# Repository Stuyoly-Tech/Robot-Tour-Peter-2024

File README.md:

View this project on [CADLAB.io](https://cadlab.io/project/28689). 

# Robot-Tour-Peter-2024
Petah

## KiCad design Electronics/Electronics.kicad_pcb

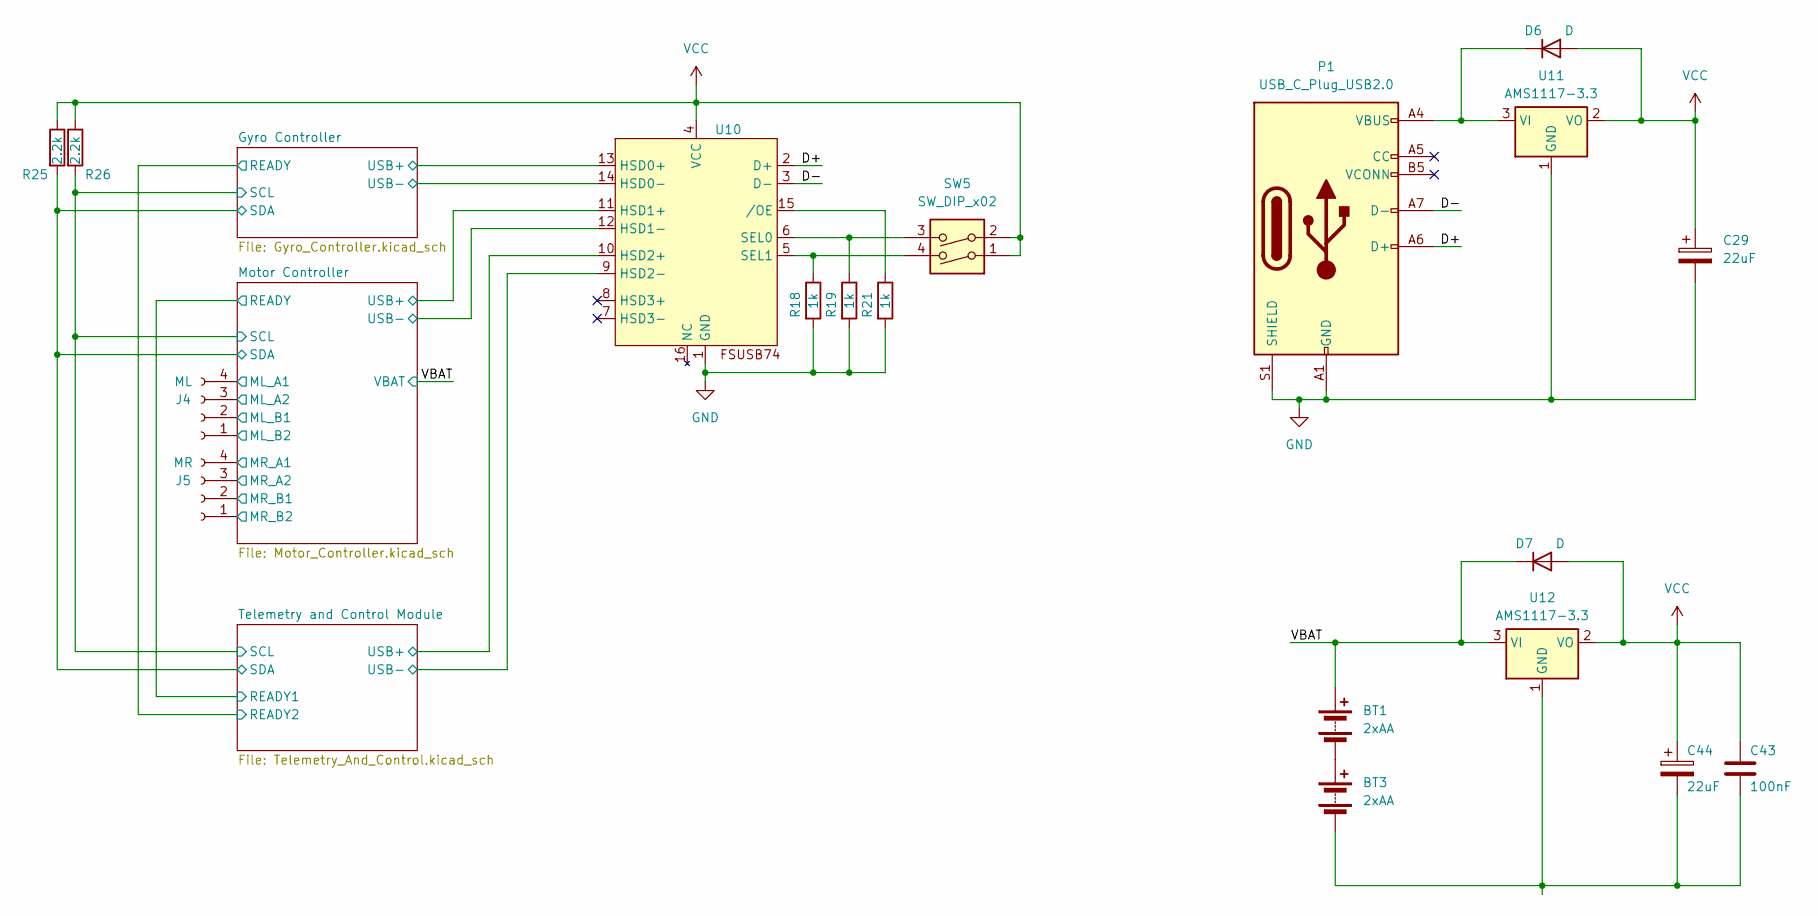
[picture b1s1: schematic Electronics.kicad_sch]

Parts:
BT1, BT3: 2xAA; BatteryHolder_Keystone_2462_2xAA
C29, C44: 22uF; CP_Elec_6.3x5.9
C43: 100nF; C_0201_0603Metric
D6, D7: D; R_0201_0603Metric
J4: ML; JST_PH_B4B-PH-K_1x04_P2.00mm_Vertical
J5: MR; JST_PH_B4B-PH-K_1x04_P2.00mm_Vertical
P1: USB_C_Plug_USB2.0; USB_C_Receptacle_Molex_105450-0101
R18, R19, R21: 1k; R_0201_0603Metric
R25, R26: 2.2k; R_0201_0603Metric
SW5: SW_DIP_x02; SW_DIP_SPSTx02_Slide_9.78x7.26mm_W8.61mm_P2.54mm
U10: QFN-16-1EP_3x3mm_P0.5mm_EP1.7x1.7mm
U11, U12: AMS1117-3.3; SOT-223-3_TabPin2

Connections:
/D+: P1.A6 (D+), U10.2 (D+)
/D-: P1.A7 (D-), U10.3 (D-)
/Gyro Controller/SCL: R26.2; also elsewhere on the board
/Gyro Controller/SDA: R25.2; also elsewhere on the board
/Gyro Controller/USB+: U10.13 (HSD0+); also elsewhere on the board
/Gyro Controller/USB-: U10.14 (HSD0-); also elsewhere on the board
/Motor Controller/ML_A1: J4.4; also elsewhere on the board
/Motor Controller/ML_A2: J4.3; also elsewhere on the board
/Motor Controller/ML_B1: J4.2; also elsewhere on the board
/Motor Controller/ML_B2: J4.1; also elsewhere on the board
/Motor Controller/MR_A1: J5.4; also elsewhere on the board
/Motor Controller/MR_A2: J5.3; also elsewhere on the board
/Motor Controller/MR_B1: J5.2; also elsewhere on the board
/Motor Controller/MR_B2: J5.1; also elsewhere on the board
/Motor Controller/USB+: U10.11 (HSD1+); also elsewhere on the board
/Motor Controller/USB-: U10.12 (HSD1-); also elsewhere on the board
/Telemetry and Control Module/USB+: U10.10 (HSD2+); also elsewhere on the board
/Telemetry and Control Module/USB-: U10.9 (HSD2-); also elsewhere on the board
/VBAT: BT1.1 (+), D7.1 (K), U12.3 (VI); also elsewhere on the board
GND: C29.2, P1.A1 (GND), P1.A12 (GND), P1.B1 (GND), P1.B12 (GND), P1.S1 (SHIELD), R18.2, R19.2, R21.2, U10.1 (GND), U11.1 (GND); also elsewhere on the board
unnamed: BT1.2 (-), BT3.1 (+)
unnamed: BT3.2 (-), C43.2, C44.2, U12.1 (GND)
unnamed: D6.1 (K), P1.A4 (VBUS), P1.A9 (VBUS), P1.B4 (VBUS), P1.B9 (VBUS), U11.3 (VI)
unnamed: R19.1, SW5.3, U10.6 (SEL0)
unnamed: R18.1, SW5.4, U10.5 (SEL1)
unnamed: R21.1, U10.15 (/OE)
VCC: C29.1, C43.1, C44.1, D6.2 (A), D7.2 (A), R25.1, R26.1, SW5.1, SW5.2, U10.4 (VCC), U11.2 (VO), U12.2 (VO); also elsewhere on the board

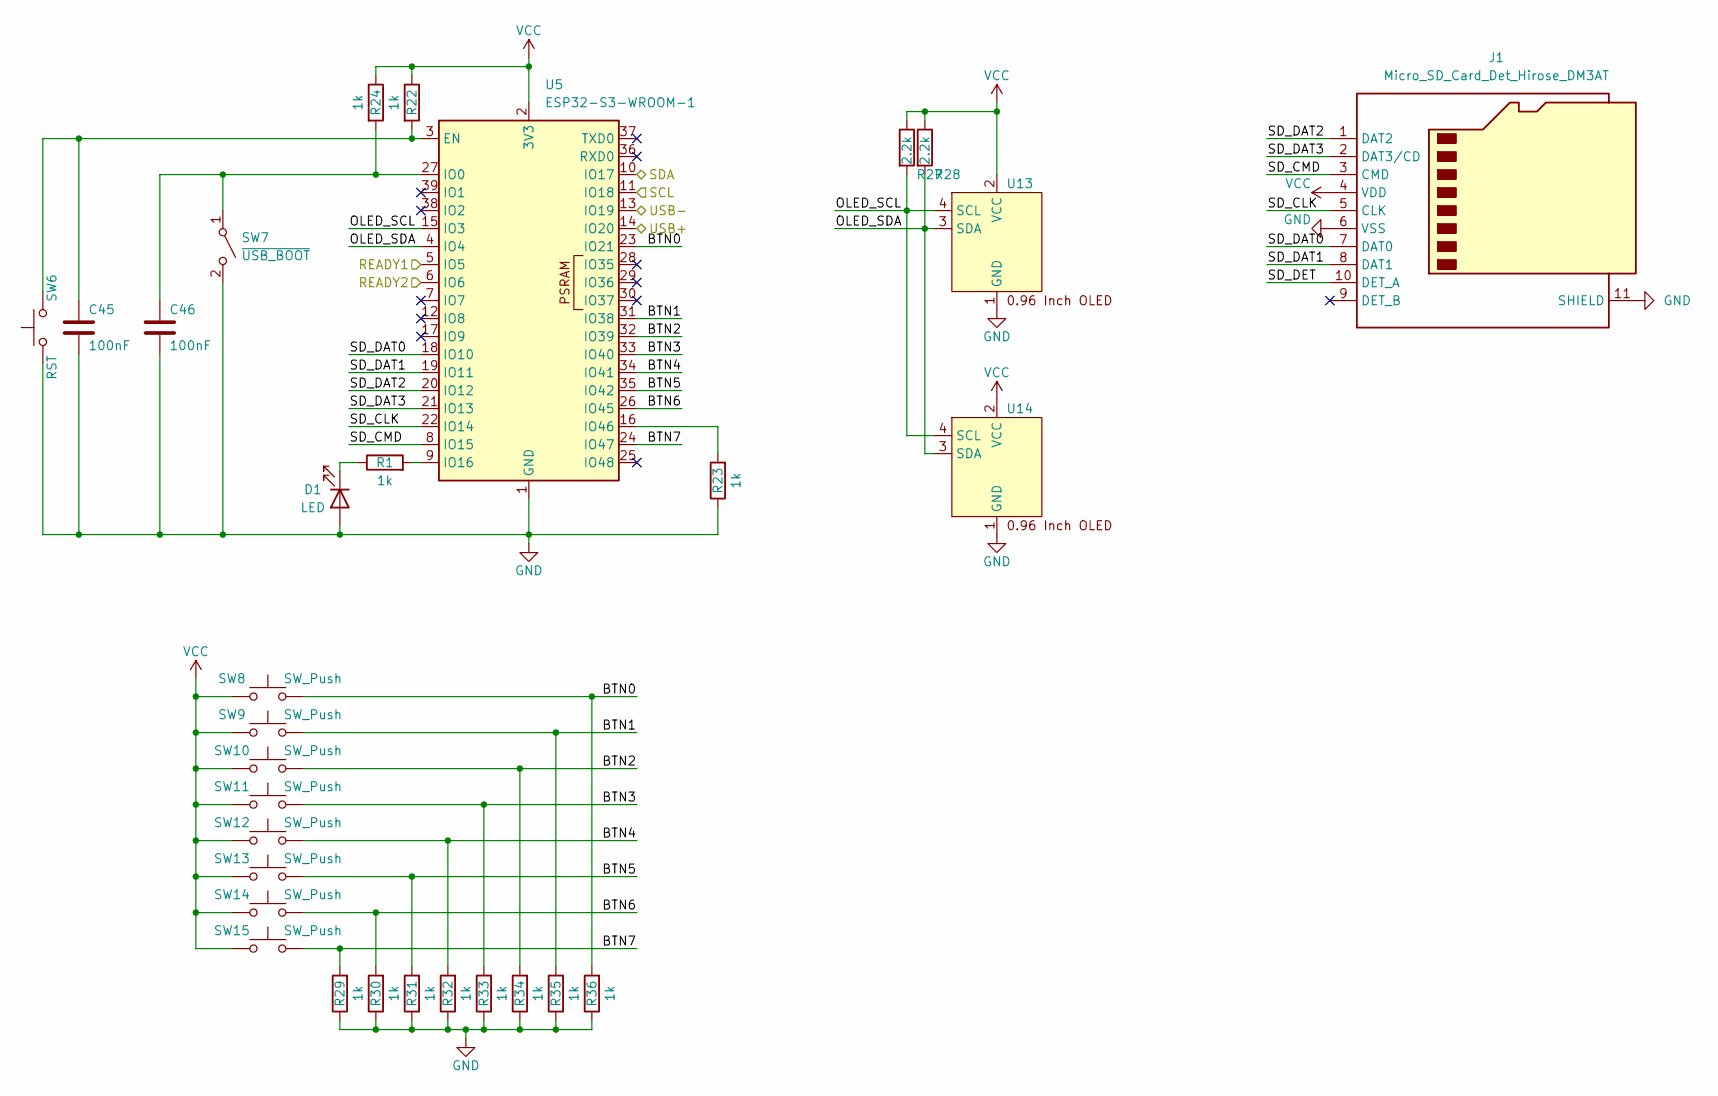
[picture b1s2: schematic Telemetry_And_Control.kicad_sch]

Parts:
C45, C46: 100nF; C_0201_0603Metric
D1: LED; LED_0603_1608Metric
J1: Micro_SD_Card_Det_Hirose_DM3AT; microSD_HC_Molex_104031-0811
R1, R22, R23, R24, R29, R30, R31, R32, R33, R34, R35, R36: 1k; R_0201_0603Metric
R27, R28: 2.2k; R_0201_0603Metric
SW6: RST; SW_SPST_TL3342
SW7: ~{USB_BOOT}; SW_DPDT_CK_JS202011JCQN
SW8, SW9, SW10, SW11, SW12, SW13, SW14, SW15: SW_Push; SW_Cherry_MX_1.00u_PCB
U5: ESP32-S3-WROOM-1
U13, U14: PinHeader_1x04_P2.54mm_Vertical

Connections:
/Gyro Controller/READY: U5.6 (IO6); also elsewhere on the board
/Gyro Controller/SCL: U5.11 (IO18); also elsewhere on the board
/Gyro Controller/SDA: U5.10 (IO17); also elsewhere on the board
/Motor Controller/READY: U5.5 (IO5); also elsewhere on the board
/Telemetry and Control Module/BTN0: R36.2, SW8.2, U5.23 (IO21)
/Telemetry and Control Module/BTN1: R35.2, SW9.2, U5.31 (IO38)
/Telemetry and Control Module/BTN2: R34.2, SW10.2, U5.32 (IO39)
/Telemetry and Control Module/BTN3: R33.2, SW11.2, U5.33 (IO40)
/Telemetry and Control Module/BTN4: R32.2, SW12.2, U5.34 (IO41)
/Telemetry and Control Module/BTN5: R31.2, SW13.2, U5.35 (IO42)
/Telemetry and Control Module/BTN6: R30.2, SW14.2, U5.26 (IO45)
/Telemetry and Control Module/BTN7: R29.2, SW15.2, U5.24 (IO47)
/Telemetry and Control Module/OLED_SCL: R27.2, U5.15 (IO3), U13.4 (SCL), U14.4 (SCL)
/Telemetry and Control Module/OLED_SDA: R28.2, U5.4 (IO4), U13.3 (SDA), U14.3 (SDA)
/Telemetry and Control Module/SD_CLK: J1.5 (CLK), U5.22 (IO14)
/Telemetry and Control Module/SD_CMD: J1.3 (CMD), U5.8 (IO15)
/Telemetry and Control Module/SD_DAT0: J1.7 (DAT0), U5.18 (IO10)
/Telemetry and Control Module/SD_DAT1: J1.8 (DAT1), U5.19 (IO11)
/Telemetry and Control Module/SD_DAT2: J1.1 (DAT2), U5.20 (IO12)
/Telemetry and Control Module/SD_DAT3: J1.2 (DAT3/CD), U5.21 (IO13)
/Telemetry and Control Module/SD_DET: J1.10 (DET_A)
/Telemetry and Control Module/USB+: U5.14 (IO20); also elsewhere on the board
/Telemetry and Control Module/USB-: U5.13 (IO19); also elsewhere on the board
GND: C45.2, C46.2, D1.2 (A), J1.6 (VSS), J1.11 (SHIELD), R23.1, R29.1, R30.1, R31.1, R32.1, R33.1, R34.1, R35.1, R36.1, SW6.1, SW7.2 (B), U5.1 (GND), U5.40 (GND), U5.41 (GND), U13.1 (GND), U14.1 (GND); also elsewhere on the board
unnamed: D1.1 (K), R1.1
unnamed: C46.1, R24.2, SW7.1 (A), U5.27 (IO0)
unnamed: C45.1, R22.2, SW6.2, U5.3 (EN)
unnamed: R1.2, U5.9 (IO16)
unnamed: R23.2, U5.16 (IO46)
VCC: J1.4 (VDD), R22.1, R24.1, R27.1, R28.1, SW8.1, SW9.1, SW10.1, SW11.1, SW12.1, SW13.1, SW14.1, SW15.1, U5.2 (3V3), U13.2 (VCC), U14.2 (VCC); also elsewhere on the board

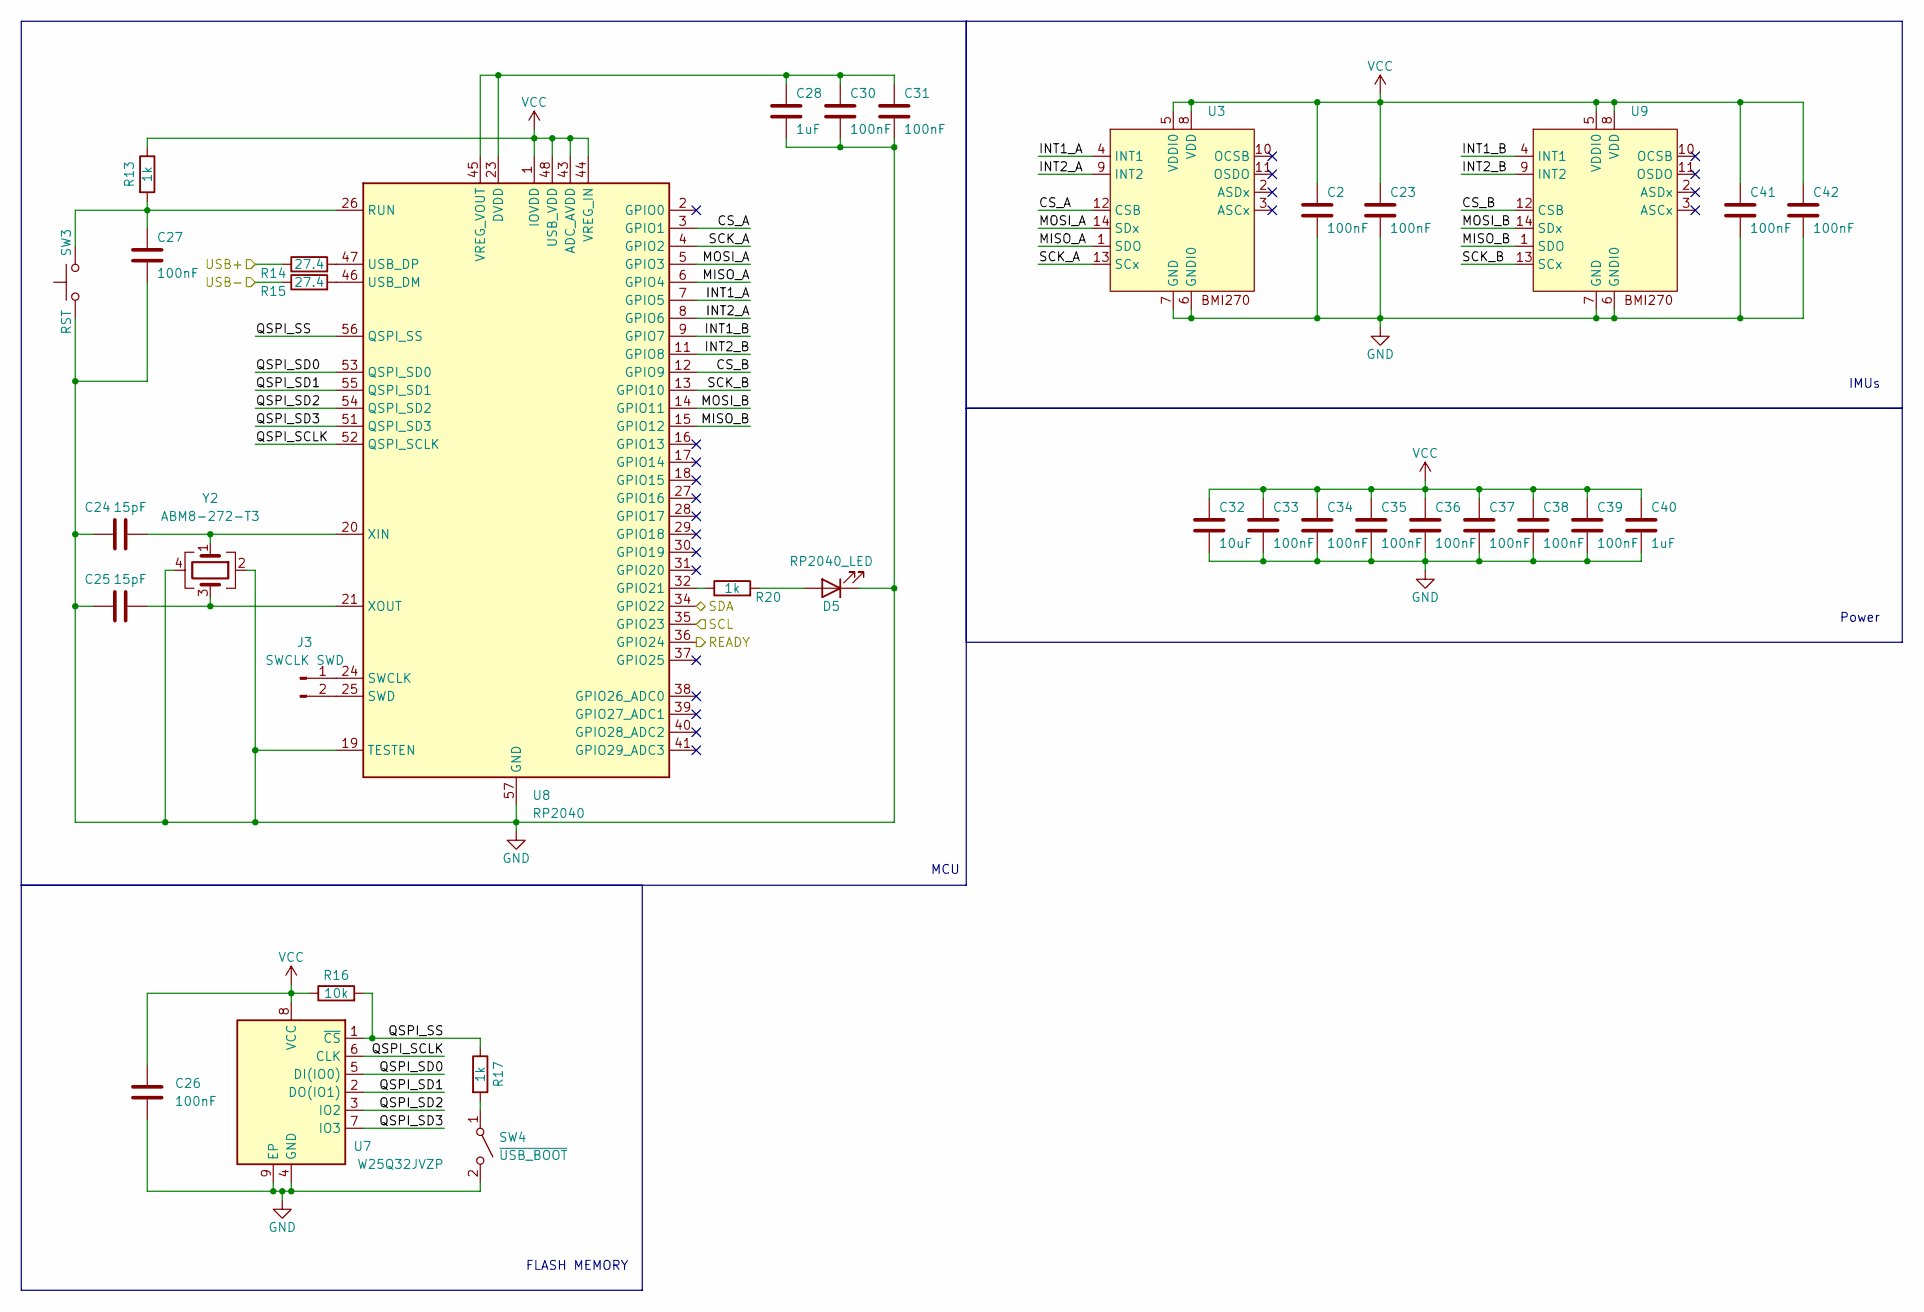
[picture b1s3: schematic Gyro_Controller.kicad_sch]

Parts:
C2, C23, C26, C27, C30, C31, C33, C34, C35, C36, C37, C38, C39, C41, C42: 100nF; C_0201_0603Metric
C24, C25: 15pF; C_0201_0603Metric
C28, C40: 1uF; C_0201_0603Metric
C32: 10uF; C_0201_0603Metric
D5: RP2040_LED; LED_0603_1608Metric
J3: SWCLK SWD; PinHeader_1x02_P2.54mm_Vertical
R13, R17, R20: 1k; R_0201_0603Metric
R14, R15: 27.4; R_0201_0603Metric
R16: 10k; R_0201_0603Metric
SW3: RST; SW_SPST_TL3342
SW4: ~{USB_BOOT}; SW_DPDT_CK_JS202011JCQN
U3, U9: Bosch_LGA-14_3x2.5mm_P0.5mm
U7: W25Q32JVZP; WSON-8-1EP_6x5mm_P1.27mm_EP3.4x4.3mm
U8: RP2040; QFN-56-1EP_7x7mm_P0.4mm_EP3.2x3.2mm
Y2: ABM8-272-T3; Crystal_SMD_Abracon_ABM8G-4Pin_3.2x2.5mm

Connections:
/Gyro Controller/CS_A: U3.12 (CSB), U8.3 (GPIO1)
/Gyro Controller/CS_B: U8.12 (GPIO9), U9.12 (CSB)
/Gyro Controller/INT1_A: U3.4 (INT1), U8.7 (GPIO5)
/Gyro Controller/INT1_B: U8.9 (GPIO7), U9.4 (INT1)
/Gyro Controller/INT2_A: U3.9 (INT2), U8.8 (GPIO6)
/Gyro Controller/INT2_B: U8.11 (GPIO8), U9.9 (INT2)
/Gyro Controller/MISO_A: U3.1 (SDO), U8.6 (GPIO4)
/Gyro Controller/MISO_B: U8.15 (GPIO12), U9.1 (SDO)
/Gyro Controller/MOSI_A: U3.14 (SDx), U8.5 (GPIO3)
/Gyro Controller/MOSI_B: U8.14 (GPIO11), U9.14 (SDx)
/Gyro Controller/QSPI_SCLK: U7.6 (CLK), U8.52 (QSPI_SCLK)
/Gyro Controller/QSPI_SD0: U7.5 (DI(IO0)), U8.53 (QSPI_SD0)
/Gyro Controller/QSPI_SD1: U7.2 (DO(IO1)), U8.55 (QSPI_SD1)
/Gyro Controller/QSPI_SD2: U7.3 (IO2), U8.54 (QSPI_SD2)
/Gyro Controller/QSPI_SD3: U7.7 (IO3), U8.51 (QSPI_SD3)
/Gyro Controller/QSPI_SS: R16.2, R17.1, U7.1 (~CS), U8.56 (QSPI_SS)
/Gyro Controller/READY: U8.36 (GPIO24); also elsewhere on the board
/Gyro Controller/SCK_A: U3.13 (SCx), U8.4 (GPIO2)
/Gyro Controller/SCK_B: U8.13 (GPIO10), U9.13 (SCx)
/Gyro Controller/SCL: U8.35 (GPIO23); also elsewhere on the board
/Gyro Controller/SDA: U8.34 (GPIO22); also elsewhere on the board
/Gyro Controller/USB+: R14.1; also elsewhere on the board
/Gyro Controller/USB-: R15.1; also elsewhere on the board
GND: C2.2, C23.2, C24.1, C25.1, C26.2, C27.2, C28.2, C30.2, C31.2, C32.2, C33.2, C34.2, C35.2, C36.2, C37.2, C38.2, C39.2, C40.2, C41.2, C42.2, D5.1 (K), SW3.1, SW4.2 (B), U3.6 (GNDI0), U3.7 (GND), U7.4 (GND), U7.9 (EP), U8.19 (TESTEN), U8.57 (GND), U9.6 (GNDI0), U9.7 (GND), Y2.2, Y2.4; also elsewhere on the board
unnamed: D5.2 (A), R20.2
unnamed: J3.1, U8.24 (SWCLK)
unnamed: J3.2, U8.25 (SWD)
unnamed: R17.2, SW4.1 (A)
unnamed: R20.1, U8.32 (GPIO21)
unnamed: C27.1, R13.2, SW3.2, U8.26 (RUN)
unnamed: R15.2, U8.46 (USB_DM)
unnamed: R14.2, U8.47 (USB_DP)
unnamed: C28.1, C30.1, C31.1, U8.23 (DVDD), U8.45 (VREG_VOUT), U8.50 (DVDD)
unnamed: C24.2, U8.20 (XIN), Y2.1
unnamed: C25.2, U8.21 (XOUT), Y2.3
VCC: C2.1, C23.1, C26.1, C32.1, C33.1, C34.1, C35.1, C36.1, C37.1, C38.1, C39.1, C40.1, C41.1, C42.1, R13.1, R16.1, U3.5 (VDDI0), U3.8 (VDD), U7.8 (VCC), U8.1 (IOVDD), U8.10 (IOVDD), U8.22 (IOVDD), U8.33 (IOVDD), U8.42 (IOVDD), U8.43 (ADC_AVDD), U8.44 (VREG_IN), U8.48 (USB_VDD), U8.49 (IOVDD), U9.5 (VDDI0), U9.8 (VDD); also elsewhere on the board

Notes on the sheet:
Power
IMUs
MCU
FLASH MEMORY

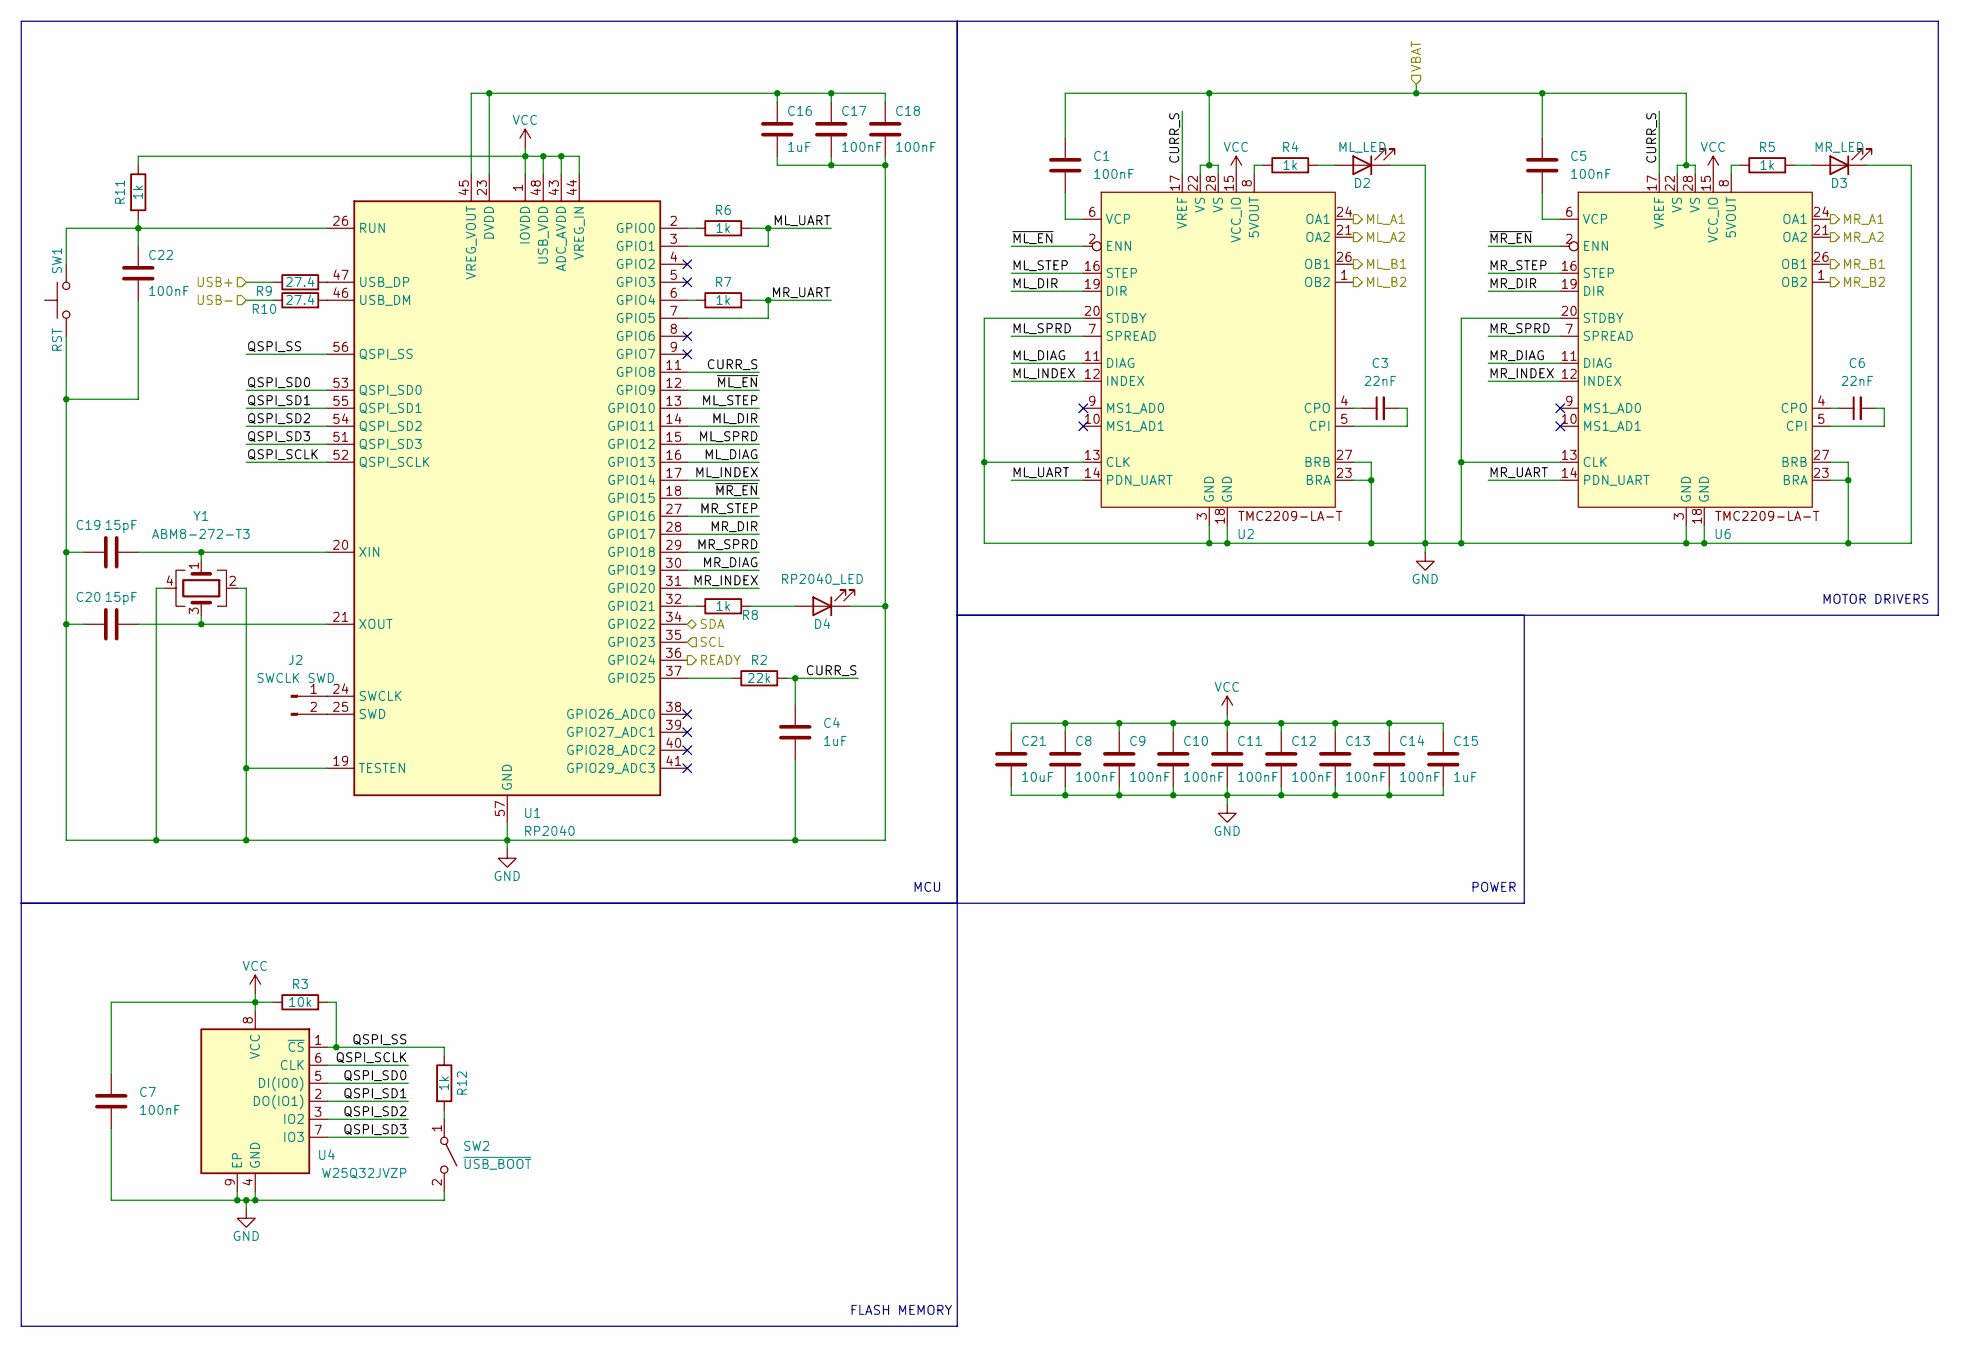
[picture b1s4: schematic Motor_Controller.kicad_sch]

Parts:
C1, C5, C7, C8, C9, C10, C11, C12, C13, C14, C17, C18, C22: 100nF; C_0201_0603Metric
C3, C6: 22nF; C_0201_0603Metric
C4, C15, C16: 1uF; C_0201_0603Metric
C19, C20: 15pF; C_0201_0603Metric
C21: 10uF; C_0201_0603Metric
D2: ML_LED; LED_0603_1608Metric
D3: MR_LED; LED_0603_1608Metric
D4: RP2040_LED; LED_0603_1608Metric
J2: SWCLK SWD; PinHeader_1x02_P2.54mm_Vertical
R2: 22k; R_0201_0603Metric
R3: 10k; R_0201_0603Metric
R4, R5, R6, R7, R8, R11, R12: 1k; R_0201_0603Metric
R9, R10: 27.4; R_0201_0603Metric
SW1: RST; SW_SPST_TL3342
SW2: ~{USB_BOOT}; SW_DPDT_CK_JS202011JCQN
U1: RP2040; QFN-56-1EP_7x7mm_P0.4mm_EP3.2x3.2mm
U2, U6: QFN-28-1EP_5x5mm_P0.5mm_EP3.75x3.75mm
U4: W25Q32JVZP; WSON-8-1EP_6x5mm_P1.27mm_EP3.4x4.3mm
Y1: ABM8-272-T3; Crystal_SMD_Abracon_ABM8G-4Pin_3.2x2.5mm

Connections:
/Gyro Controller/SCL: U1.35 (GPIO23); also elsewhere on the board
/Gyro Controller/SDA: U1.34 (GPIO22); also elsewhere on the board
/Motor Controller/CURR_S: C4.1, R2.2, U1.11 (GPIO8), U2.17 (VREF), U6.17 (VREF)
/Motor Controller/ML_A1: U2.24 (OA1); also elsewhere on the board
/Motor Controller/ML_A2: U2.21 (OA2); also elsewhere on the board
/Motor Controller/ML_B1: U2.26 (OB1); also elsewhere on the board
/Motor Controller/ML_B2: U2.1 (OB2); also elsewhere on the board
/Motor Controller/ML_DIAG: U1.16 (GPIO13), U2.11 (DIAG)
/Motor Controller/ML_DIR: U1.14 (GPIO11), U2.19 (DIR)
/Motor Controller/ML_INDEX: U1.17 (GPIO14), U2.12 (INDEX)
/Motor Controller/ML_SPRD: U1.15 (GPIO12), U2.7 (SPREAD)
/Motor Controller/ML_STEP: U1.13 (GPIO10), U2.16 (STEP)
/Motor Controller/ML_UART: R6.2, U1.3 (GPIO1), U2.14 (PDN_UART)
/Motor Controller/MR_A1: U6.24 (OA1); also elsewhere on the board
/Motor Controller/MR_A2: U6.21 (OA2); also elsewhere on the board
/Motor Controller/MR_B1: U6.26 (OB1); also elsewhere on the board
/Motor Controller/MR_B2: U6.1 (OB2); also elsewhere on the board
/Motor Controller/MR_DIAG: U1.30 (GPIO19), U6.11 (DIAG)
/Motor Controller/MR_DIR: U1.28 (GPIO17), U6.19 (DIR)
/Motor Controller/MR_INDEX: U1.31 (GPIO20), U6.12 (INDEX)
/Motor Controller/MR_SPRD: U1.29 (GPIO18), U6.7 (SPREAD)
/Motor Controller/MR_STEP: U1.27 (GPIO16), U6.16 (STEP)
/Motor Controller/MR_UART: R7.2, U1.7 (GPIO5), U6.14 (PDN_UART)
/Motor Controller/QSPI_SCLK: U1.52 (QSPI_SCLK), U4.6 (CLK)
/Motor Controller/QSPI_SD0: U1.53 (QSPI_SD0), U4.5 (DI(IO0))
/Motor Controller/QSPI_SD1: U1.55 (QSPI_SD1), U4.2 (DO(IO1))
/Motor Controller/QSPI_SD2: U1.54 (QSPI_SD2), U4.3 (IO2)
/Motor Controller/QSPI_SD3: U1.51 (QSPI_SD3), U4.7 (IO3)
/Motor Controller/QSPI_SS: R3.2, R12.1, U1.56 (QSPI_SS), U4.1 (~CS)
/Motor Controller/READY: U1.36 (GPIO24); also elsewhere on the board
/Motor Controller/USB+: R9.1; also elsewhere on the board
/Motor Controller/USB-: R10.1; also elsewhere on the board
/Motor Controller/~ML_EN: U1.12 (GPIO9), U2.2 (ENN)
/Motor Controller/~MR_EN: U1.18 (GPIO15), U6.2 (ENN)
/VBAT: C1.1, C5.1, U2.22 (VS), U2.28 (VS), U6.22 (VS), U6.28 (VS); also elsewhere on the board
GND: C4.2, C7.2, C8.2, C9.2, C10.2, C11.2, C12.2, C13.2, C14.2, C15.2, C16.2, C17.2, C18.2, C19.1, C20.1, C21.2, C22.2, D2.1 (K), D3.1 (K), D4.1 (K), SW1.1, SW2.2 (B), U1.19 (TESTEN), U1.57 (GND), U2.3 (GND), U2.13 (CLK), U2.18 (GND), U2.20 (STDBY), U2.23 (BRA), U2.27 (BRB), U4.4 (GND), U4.9 (EP), U6.3 (GND), U6.13 (CLK), U6.18 (GND), U6.20 (STDBY), U6.23 (BRA), U6.27 (BRB), Y1.2, Y1.4; also elsewhere on the board
unnamed: D2.2 (A), R4.2
unnamed: D3.2 (A), R5.2
unnamed: D4.2 (A), R8.2
unnamed: J2.1, U1.24 (SWCLK)
unnamed: J2.2, U1.25 (SWD)
unnamed: R12.2, SW2.1 (A)
unnamed: R6.1, U1.2 (GPIO0)
unnamed: R7.1, U1.6 (GPIO4)
unnamed: R8.1, U1.32 (GPIO21)
unnamed: R2.1, U1.37 (GPIO25)
unnamed: C22.1, R11.2, SW1.2, U1.26 (RUN)
unnamed: R10.2, U1.46 (USB_DM)
unnamed: R9.2, U1.47 (USB_DP)
unnamed: C16.1, C17.1, C18.1, U1.23 (DVDD), U1.45 (VREG_VOUT), U1.50 (DVDD)
unnamed: C19.2, U1.20 (XIN), Y1.1
unnamed: C20.2, U1.21 (XOUT), Y1.3
unnamed: R4.1, U2.8 (5VOUT)
unnamed: C3.2, U2.5 (CPI)
unnamed: C3.1, U2.4 (CPO)
unnamed: C1.2, U2.6 (VCP)
unnamed: R5.1, U6.8 (5VOUT)
unnamed: C6.2, U6.5 (CPI)
unnamed: C6.1, U6.4 (CPO)
unnamed: C5.2, U6.6 (VCP)
VCC: C7.1, C8.1, C9.1, C10.1, C11.1, C12.1, C13.1, C14.1, C15.1, C21.1, R3.1, R11.1, U1.1 (IOVDD), U1.10 (IOVDD), U1.22 (IOVDD), U1.33 (IOVDD), U1.42 (IOVDD), U1.43 (ADC_AVDD), U1.44 (VREG_IN), U1.48 (USB_VDD), U1.49 (IOVDD), U2.15 (VCC_IO), U4.8 (VCC), U6.15 (VCC_IO); also elsewhere on the board

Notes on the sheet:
MCU
FLASH MEMORY
POWER
MOTOR DRIVERS

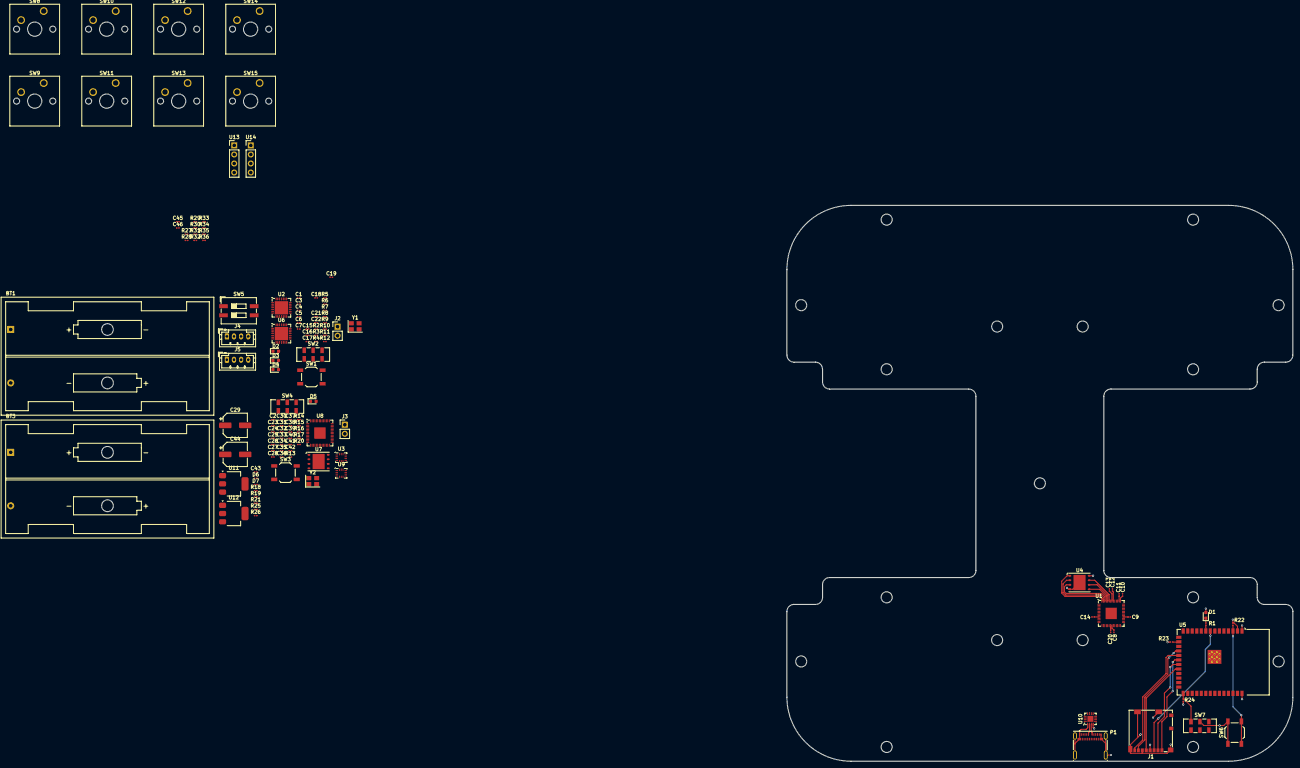
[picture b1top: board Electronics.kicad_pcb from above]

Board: 4 copper layers, 142.0 x 156.0 mm, 128 parts (0 on the bottom side), 124 nets.

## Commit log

2024-11-25 Backlink to CADLAB.io has been added.
2024-11-26 components for motor controller
2024-11-26 started esp32
2024-12-04 symbol library
2024-12-04 TMC2209 FOOTPRINT + SCHEMATIC
2024-12-04 BMI270 but fr this time
2024-12-04 BMI270 schem
2024-12-04 update gitignore
2024-12-05 motor driver finished!
2024-12-09 gyros done
2024-12-09 rename telemetry
2024-12-09 CP2102-GM Symbol
2024-12-09 power + usb
2024-12-11 USB to UART converter
2024-12-13 mostly done, needs review, needs pins
2024-12-17 oled displays
2024-12-17 buttons
2024-12-18 started pcb, need bigger frame
2024-12-19 routing started
2025-01-07 routing esp32 motor controller, need to read up on diff pair
